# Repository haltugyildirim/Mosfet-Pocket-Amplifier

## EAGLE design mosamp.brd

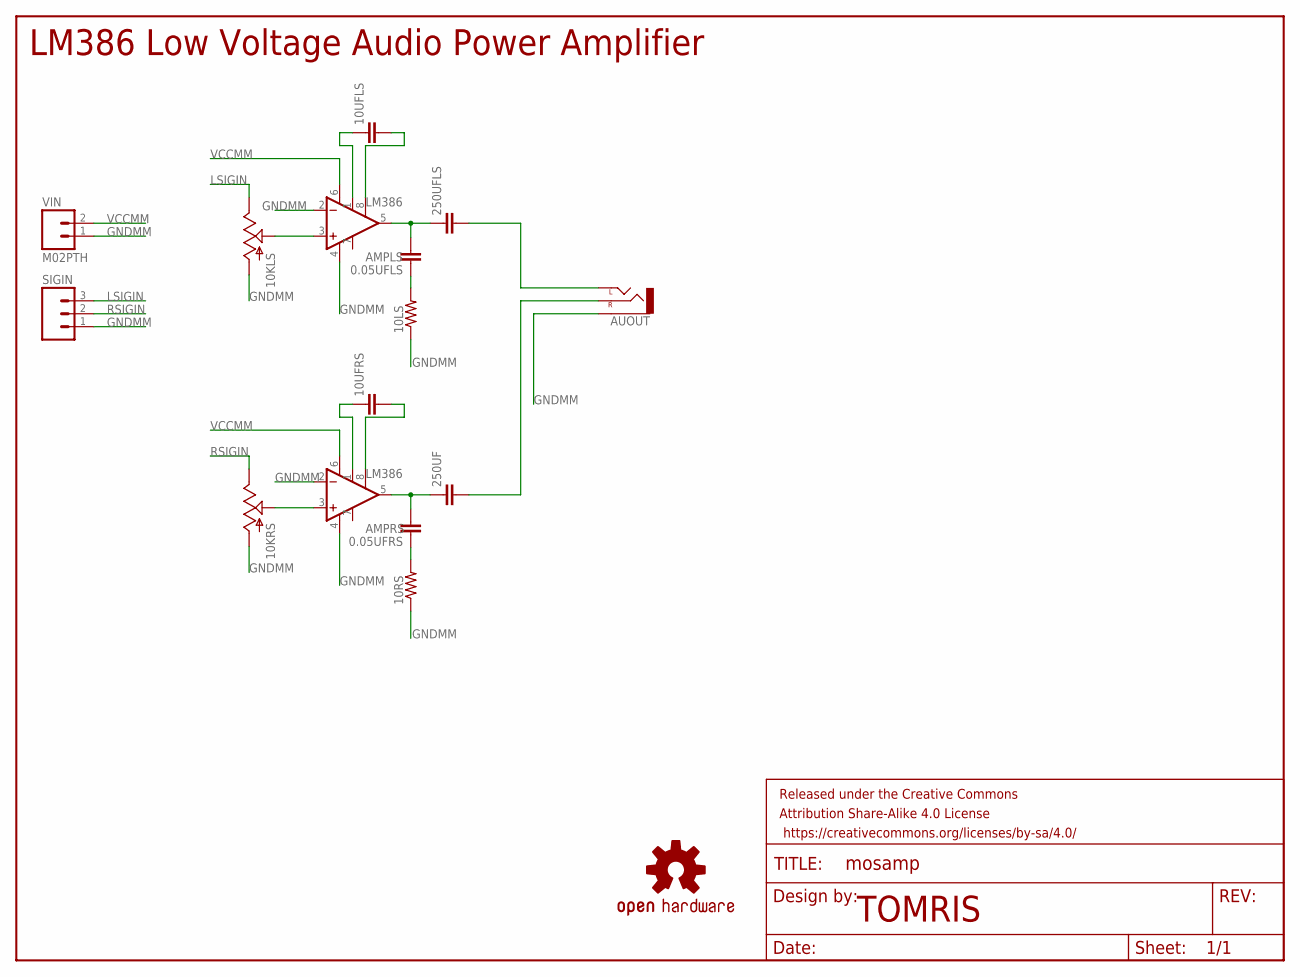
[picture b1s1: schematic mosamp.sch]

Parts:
0.05UFLS, 0.05UFRS, 10UFLS, 10UFRS, 250UF, 250UFLS: CAPPTH; CAP-PTH-SMALL
10KLS, 10KRS: POTMAM; POT_MAMMOTH
10LS, 10RS: RESISTORAXIAL-0.3; AXIAL-0.3
AMPLS: LM386; DIP08
AMPRS: LM386; DIP08
AUOUT: AUDIO-JACK2.5MM; STEREOJACK2.5MM_STEREOJACK2.5MM
FRAME1: FRAME-LETTER; CREATIVE_COMMONS
LOGO1: OSHW-LOGOM; OSHW-LOGO-M
SIGIN: M03PTH; 1X03
VIN: M02PTH; 1X02

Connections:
GNDMM: 10KLS.P$2 (A), 10KRS.P$2 (A), 10LS.P$1 (1), 10RS.P$1 (1), AMPLS.2 (-IN), AMPLS.4 (V-), AMPRS.2 (-IN), AMPRS.4 (V-), AUOUT.RING1 (SLEEVE), SIGIN.1, VIN.1
LSIGIN: 10KLS.P$3 (E), SIGIN.3
unnamed: 10UFRS.1, AMPRS.1 (GAIN)
unnamed: 10UFRS.2, AMPRS.8 (GAIN)
unnamed: 0.05UFRS.2, 250UF.1, AMPRS.5 (OUT)
unnamed: 10KRS.P$1 (S), AMPRS.3 (+IN)
unnamed: 250UFLS.2, AUOUT.SHIELD (LEFT)
unnamed: 250UF.2, AUOUT.TIP (RIGHT)
unnamed: 0.05UFRS.1, 10RS.P$2 (2)
unnamed: 10UFLS.1, AMPLS.1 (GAIN)
unnamed: 10UFLS.2, AMPLS.8 (GAIN)
unnamed: 0.05UFLS.2, 250UFLS.1, AMPLS.5 (OUT)
unnamed: 10KLS.P$1 (S), AMPLS.3 (+IN)
unnamed: 0.05UFLS.1, 10LS.P$2 (2)
RSIGIN: 10KRS.P$3 (E), SIGIN.2
VCCMM: AMPLS.6 (V+), AMPRS.6 (V+), VIN.2

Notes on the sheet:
TOMRIS
LM386 Low Voltage Audio Power Amplifier

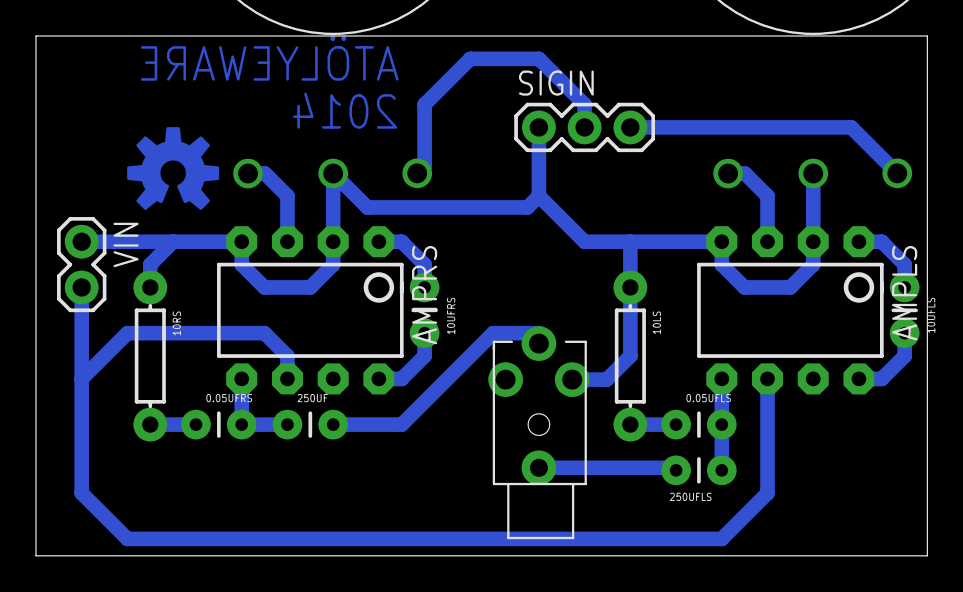
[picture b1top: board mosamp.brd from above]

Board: 2 copper layers, 49.5 x 28.9 mm, 17 parts (0 on the bottom side), 16 nets.

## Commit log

2016-08-26 initial design files
    adding initial design

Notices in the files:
parts and their libraries:
SparkFun-Capacitors: Licensing: Creative Commons ShareAlike 4.0 International - https://creativecommons.org/licenses/by-sa/4.0
SparkFun-Aesthetics: Released under the Creative Commons Attribution Share-Alike 4.0 License
SparkFun-Aesthetics: https://creativecommons.org/licenses/by-sa/4.0
